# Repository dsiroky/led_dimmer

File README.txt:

Simple and compact 12 V LED dimmer
==================================

KiCad sources.

Dimming by a potentiometer. Device can drive up to 50 W. It depends on the transistor Q1. Good one can be e.g. TSM2314CX (http://www.farnell.com/datasheets/1685598.pdf).

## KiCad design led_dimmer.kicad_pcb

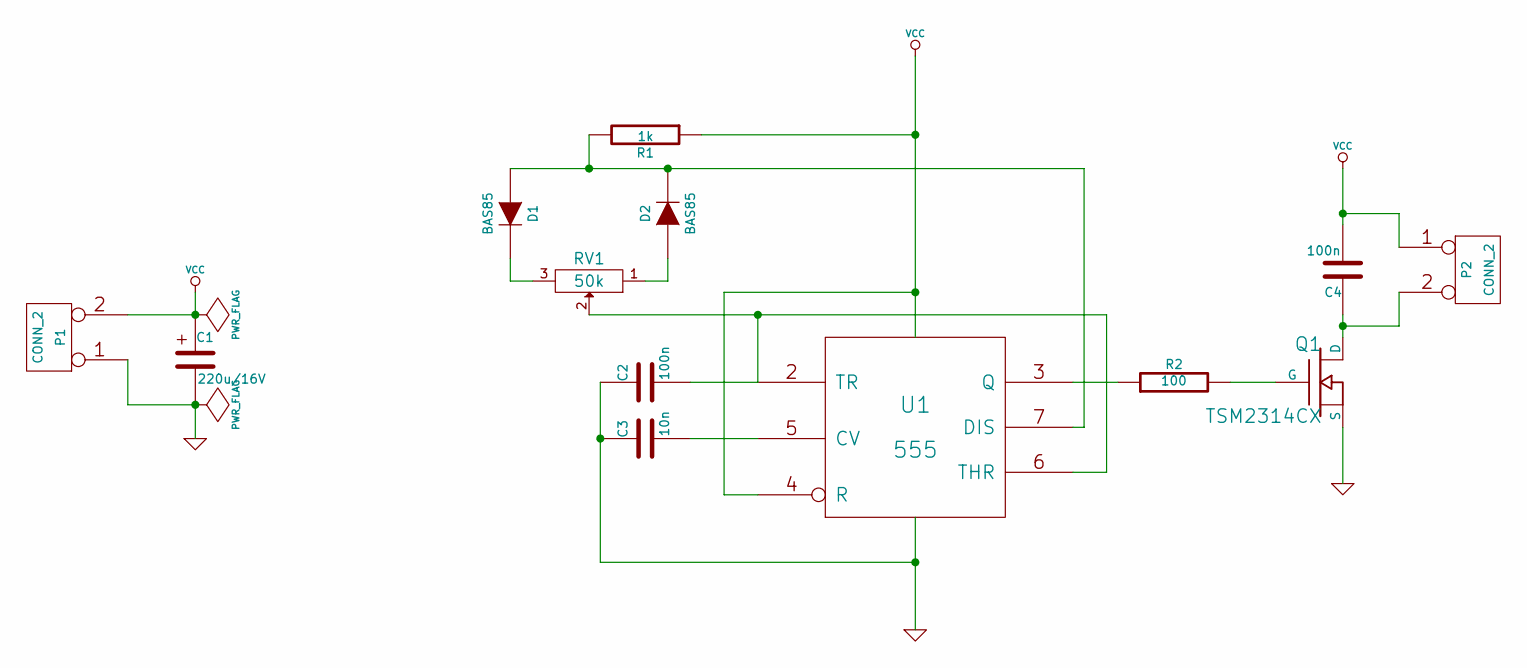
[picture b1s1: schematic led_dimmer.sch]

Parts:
C1: 220u/16V
C2, C4: 100n
C3: 10n
D1, D2: BAS85
P1, P2: CONN_2
Q1: TSM2314CX
R1: 1k
R2: 100
RV1: 50k
U1: 555

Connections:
GND: C1.2, C2.1, C3.1, P1.1, Q1.S, U1.1 (GND)
unnamed: C2.2, RV1.2, U1.2 (TR), U1.6 (THR)
unnamed: C3.2, U1.5 (CV)
unnamed: C4.1, P2.2 (PM), Q1.D
unnamed: D1.1 (A), D2.2 (K), R1.2, U1.7 (DIS)
unnamed: D1.2 (K), RV1.3
unnamed: D2.1 (A), RV1.1
unnamed: Q1.G, R2.2
unnamed: R2.1, U1.3 (Q)
VCC: C1.1, C4.2, P1.2 (PM), P2.1, R1.1, U1.4 (R), U1.8 (VCC)

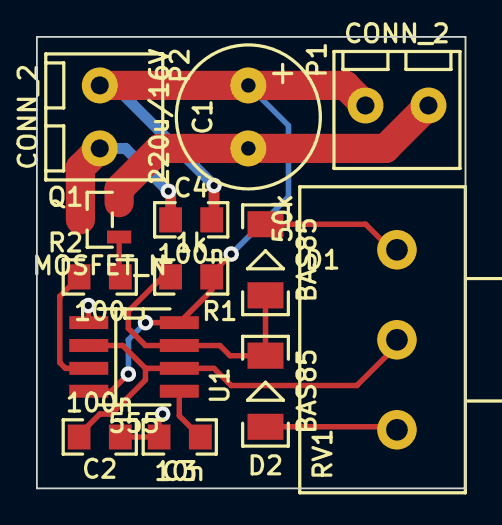
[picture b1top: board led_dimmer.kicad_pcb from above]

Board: 2 copper layers, 23.8 x 25.1 mm, 13 parts (0 on the bottom side), 10 nets.

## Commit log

2014-02-04 initial import
2014-02-04 larger vias, silk screen update
2014-02-04 readme and license
2014-02-04 drill file update
2014-02-04 removed redundant vias
2014-02-25 tweaks
2014-02-27 bottom silk fixes, power connector turned
2014-02-27 gerber files update
